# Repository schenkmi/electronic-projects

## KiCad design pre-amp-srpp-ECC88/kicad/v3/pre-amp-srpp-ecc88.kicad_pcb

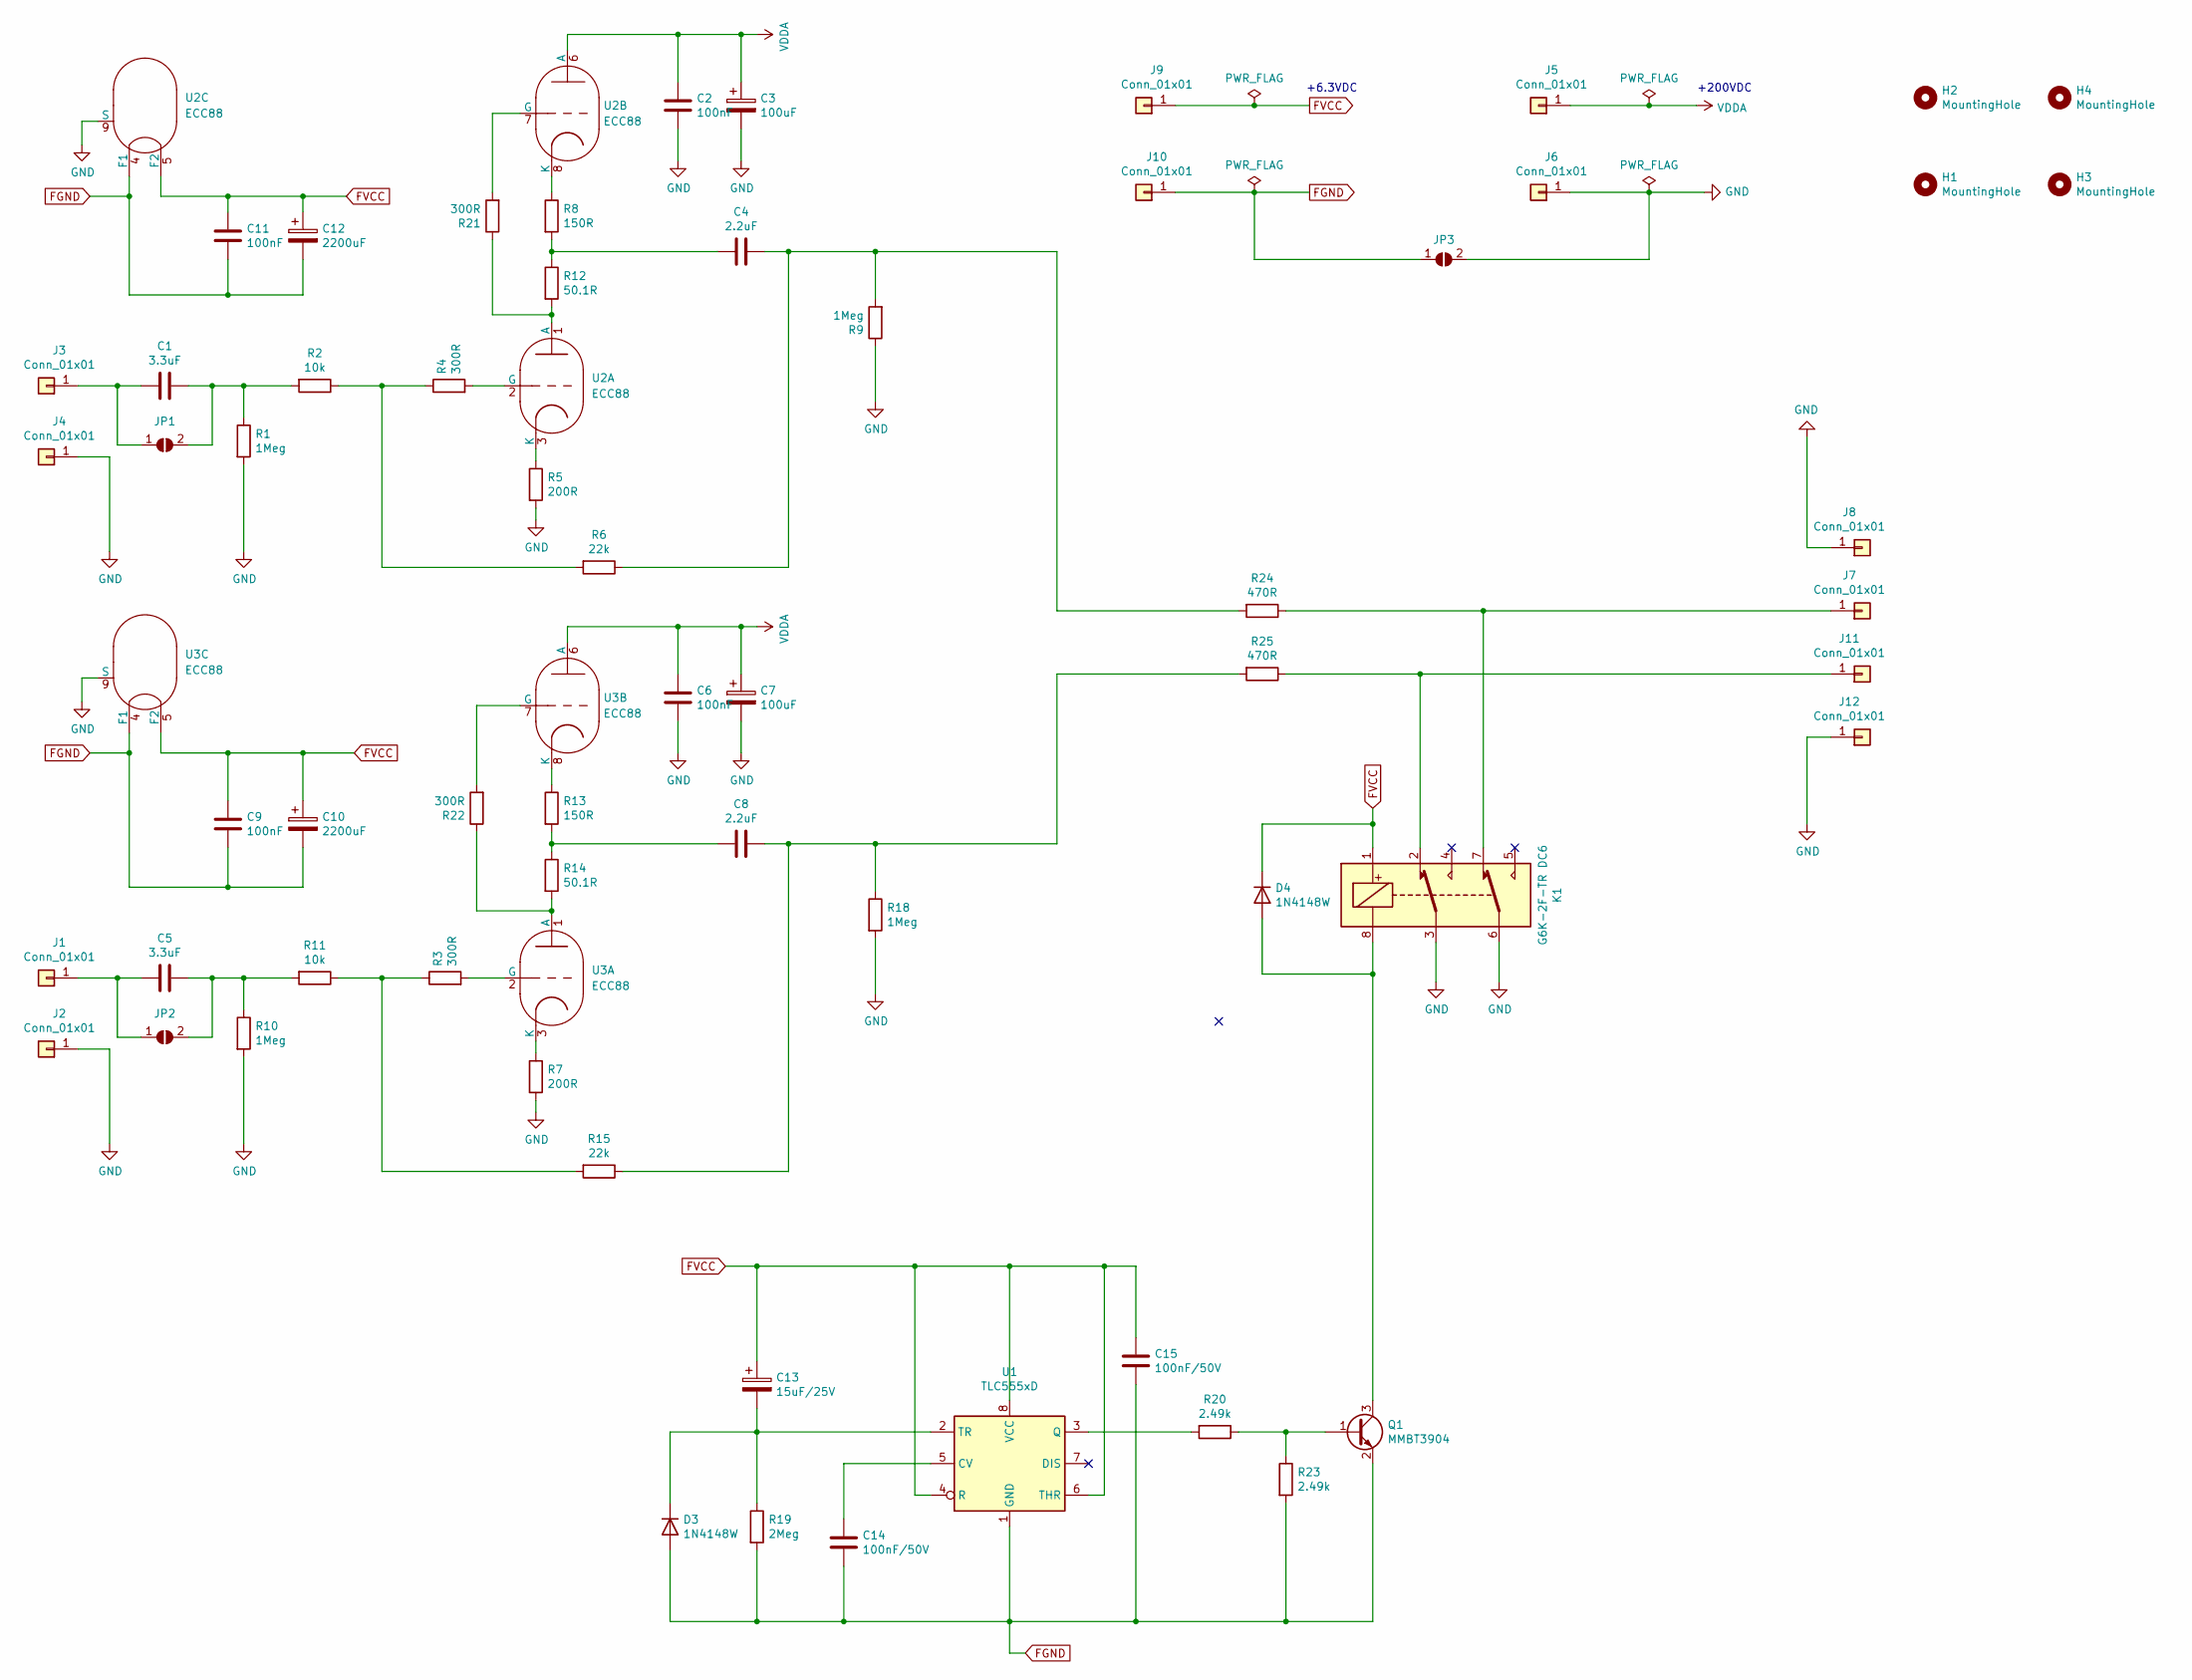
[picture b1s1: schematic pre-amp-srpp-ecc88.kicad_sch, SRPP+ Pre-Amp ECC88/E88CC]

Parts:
C1, C5: 3.3uF; C_Rect_L7.2mm_W7.2mm_P5.00mm_FKS2_FKP2_MKS2_MKP2
C2, C6: 100nF; C_Rect_L16.5mm_W5.0mm_P15.00mm_MKT
C3, C7: 100uF; CP_Radial_D18.0mm_P7.50mm
C4, C8: 2.2uF; C_Rect_L31.5mm_W11.0mm_P27.50mm_MKS4
C9, C11: 100nF; C_Rect_L7.2mm_W2.5mm_P5.00mm_FKS2_FKP2_MKS2_MKP2
C10, C12: 2200uF; CP_Radial_D16.0mm_P7.50mm
C13: 15uF/25V; CP_EIA-3216-12_Kemet-S_Pad1.58x1.35mm_HandSolder
C14, C15: 100nF/50V; C_0805_2012Metric_Pad1.18x1.45mm_HandSolder
D3, D4: 1N4148W; D_SOD-123
H1, H2, H3, H4: MountingHole; MountingHole_3.2mm_M3
J1, J2, J3, J4, J7, J8, J11, J12: Conn_01x01; Pin_D1.0mm_L10.0mm
J5, J6, J9, J10: Conn_01x01; Pin_D1.3mm_L11.0mm
JP1, JP2, JP3: SolderJumper_2_Open; SolderJumper-2_P1.3mm_Open_Pad1.0x1.5mm
K1: G6K-2F-TR DC6; Relay_DPDT_Omron_G6K-2F
Q1: MMBT3904; SOT-23
R1, R9, R10, R18: 1Meg; R_MELF_MMB-0207
R2, R11: 10k; R_MELF_MMB-0207
R3, R4, R21, R22: 300R; R_MELF_MMB-0207
R5, R7: 200R; R_MELF_MMB-0207
R6, R15: 22k; R_MELF_MMB-0207
R8, R13: 150R; R_MELF_MMB-0207
R12, R14: 50.1R; R_MELF_MMB-0207
R19: 2Meg; R_0805_2012Metric_Pad1.20x1.40mm_HandSolder
R20, R23: 2.49k; R_0805_2012Metric_Pad1.20x1.40mm_HandSolder
R24, R25: 470R; R_MELF_MMB-0207
U1: TLC555xD; SOIC-8_3.9x4.9mm_P1.27mm
U2, U3: ECC88; socket_gzc9-b

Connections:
FGND: C9.2, C10.2, C11.2, C12.2, C14.2, C15.2, D3.2 (A), J10.1, JP3.1 (A), Q1.2 (E), R19.2, R23.2, U1.1 (GND), U2.4 (F1), U3.4 (F1)
FVCC: C9.1, C10.1, C11.1, C12.1, C13.1, C15.1, D4.1 (K), J9.1, K1.1, U1.4 (R), U1.6 (THR), U1.8 (VCC), U2.5 (F2), U3.5 (F2)
GND: C2.2, C3.2, C6.2, C7.2, J2.1, J4.1, J6.1, J8.1, J12.1, JP3.2 (B), K1.3, K1.6, R1.2, R5.2, R7.2, R9.1, R10.2, R18.2, U2.9 (S), U3.9 (S)
unnamed: C1.1, JP1.2 (B), R1.1, R2.2
unnamed: C1.2, J3.1, JP1.1 (A)
unnamed: C4.1, R6.1, R9.2, R24.2
unnamed: C4.2, R8.2, R12.1
unnamed: C5.1, JP2.2 (B), R10.1, R11.2
unnamed: C5.2, J1.1, JP2.1 (A)
unnamed: C8.1, R15.1, R18.1, R25.2
unnamed: C8.2, R13.2, R14.1
unnamed: C13.2, D3.1 (K), R19.1, U1.2 (TR)
unnamed: C14.1, U1.5 (CV)
unnamed: D4.2 (A), K1.8, Q1.3 (C)
unnamed: J7.1, K1.7, R24.1
unnamed: J11.1, K1.2, R25.1
unnamed: Q1.1 (B), R20.1, R23.1
unnamed: R2.1, R4.1, R6.2
unnamed: R3.2, U3.2 (G)
unnamed: R4.2, U2.2 (G)
unnamed: R5.1, U2.3 (K)
unnamed: R7.1, U3.3 (K)
unnamed: R8.1, U2.8 (K)
unnamed: R3.1, R11.1, R15.2
unnamed: R12.2, R21.1, U2.1 (A)
unnamed: R13.1, U3.8 (K)
unnamed: R14.2, R22.1, U3.1 (A)
unnamed: R20.2, U1.3 (Q)
unnamed: R21.2, U2.7 (G)
unnamed: R22.2, U3.7 (G)
VDDA: C2.1, C3.1, C6.1, C7.1, J5.1, U2.6 (A), U3.6 (A)

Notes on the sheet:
+6.3VDC
+200VDC

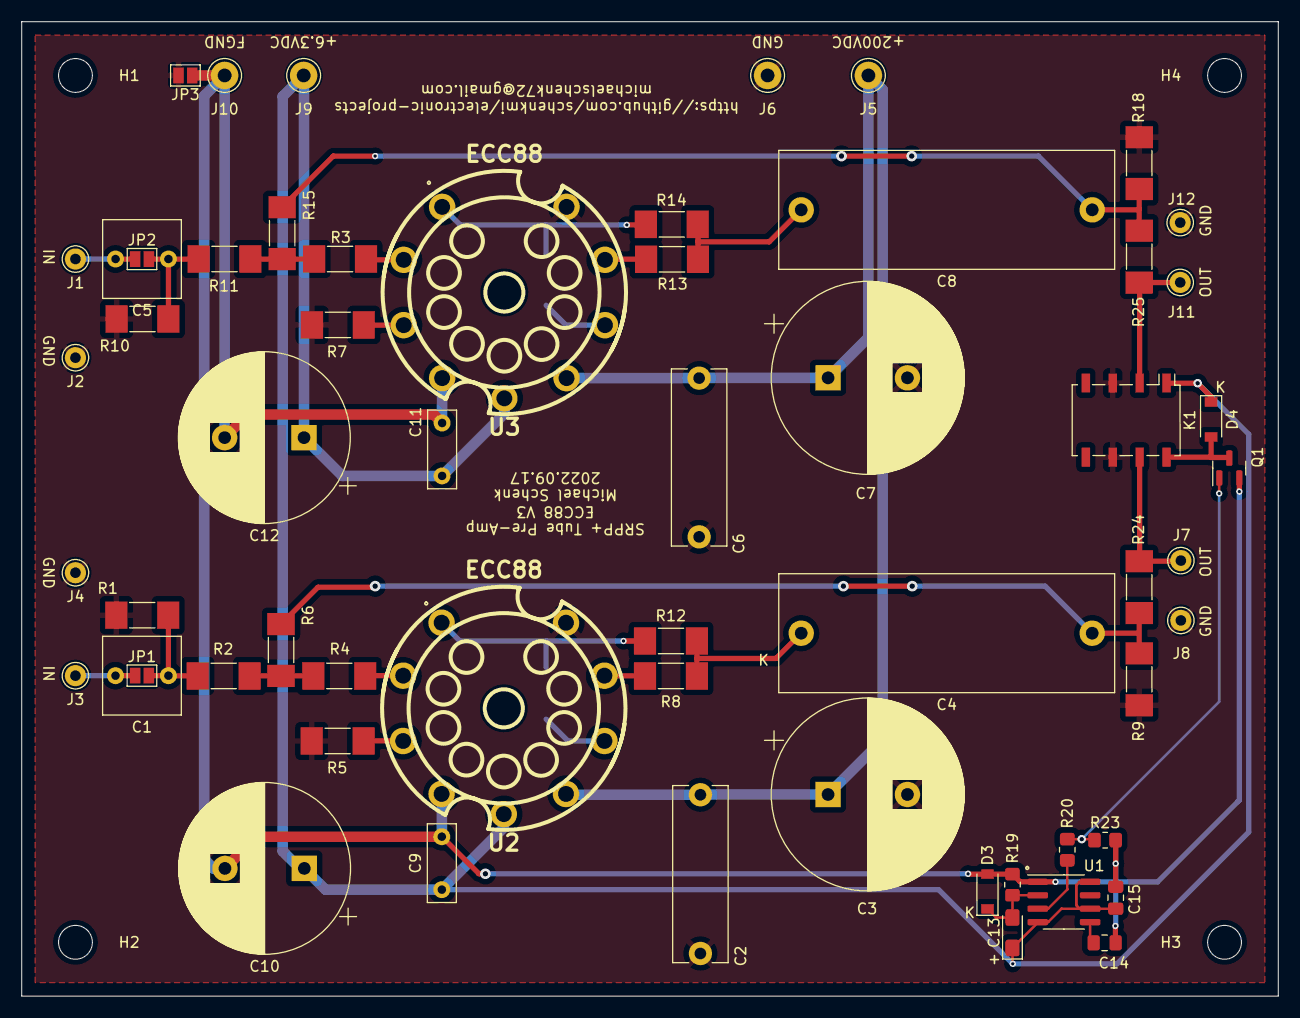
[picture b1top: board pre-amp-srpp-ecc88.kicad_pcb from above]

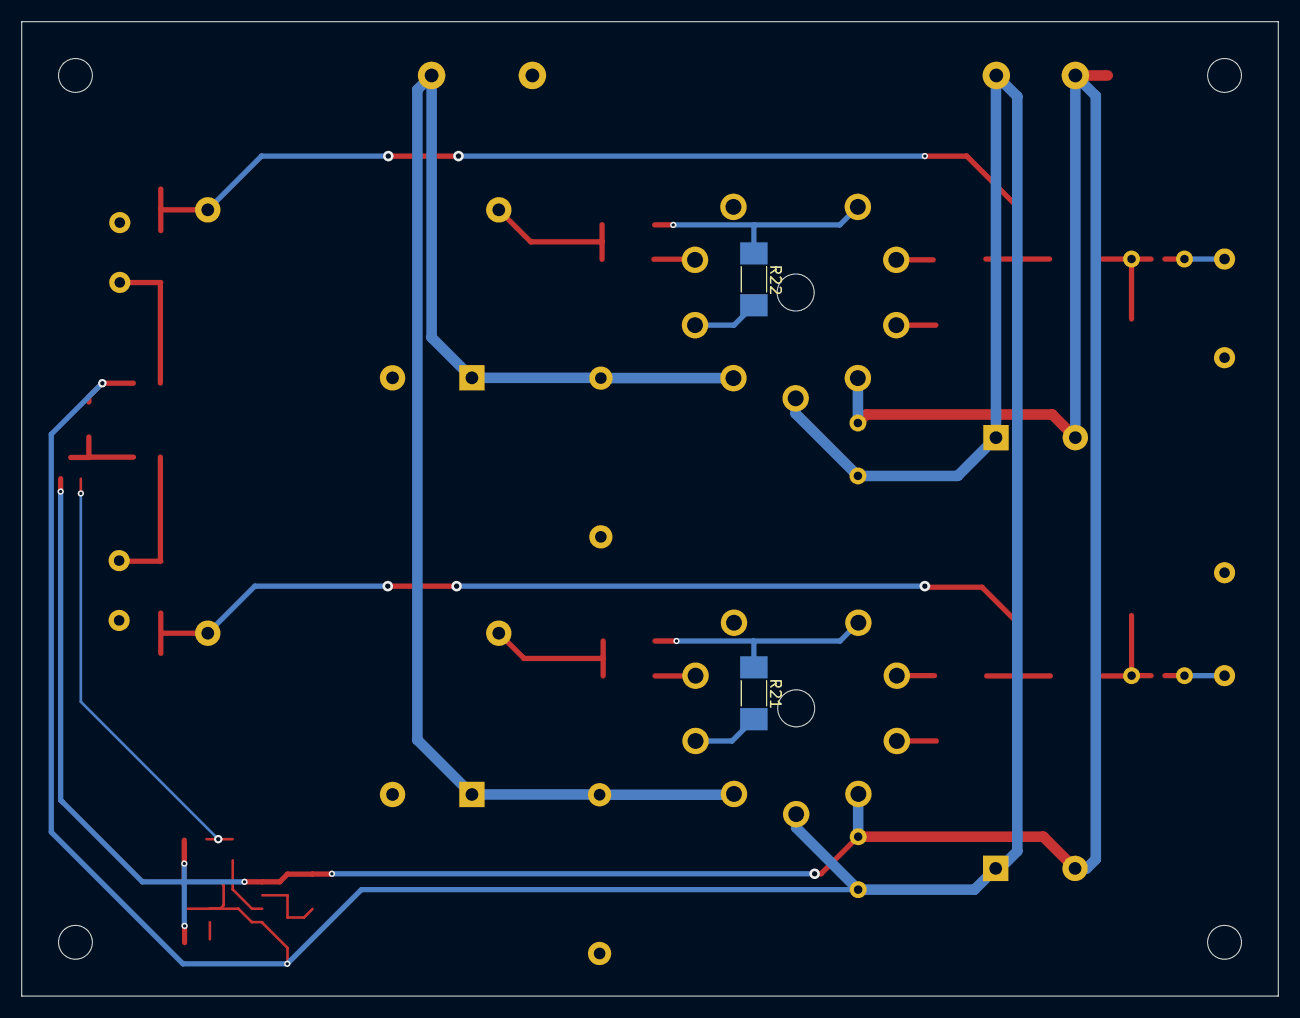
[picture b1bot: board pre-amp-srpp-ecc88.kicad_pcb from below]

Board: 2 copper layers, 118.7 x 92.1 mm, 64 parts (2 on the bottom side), 31 nets.

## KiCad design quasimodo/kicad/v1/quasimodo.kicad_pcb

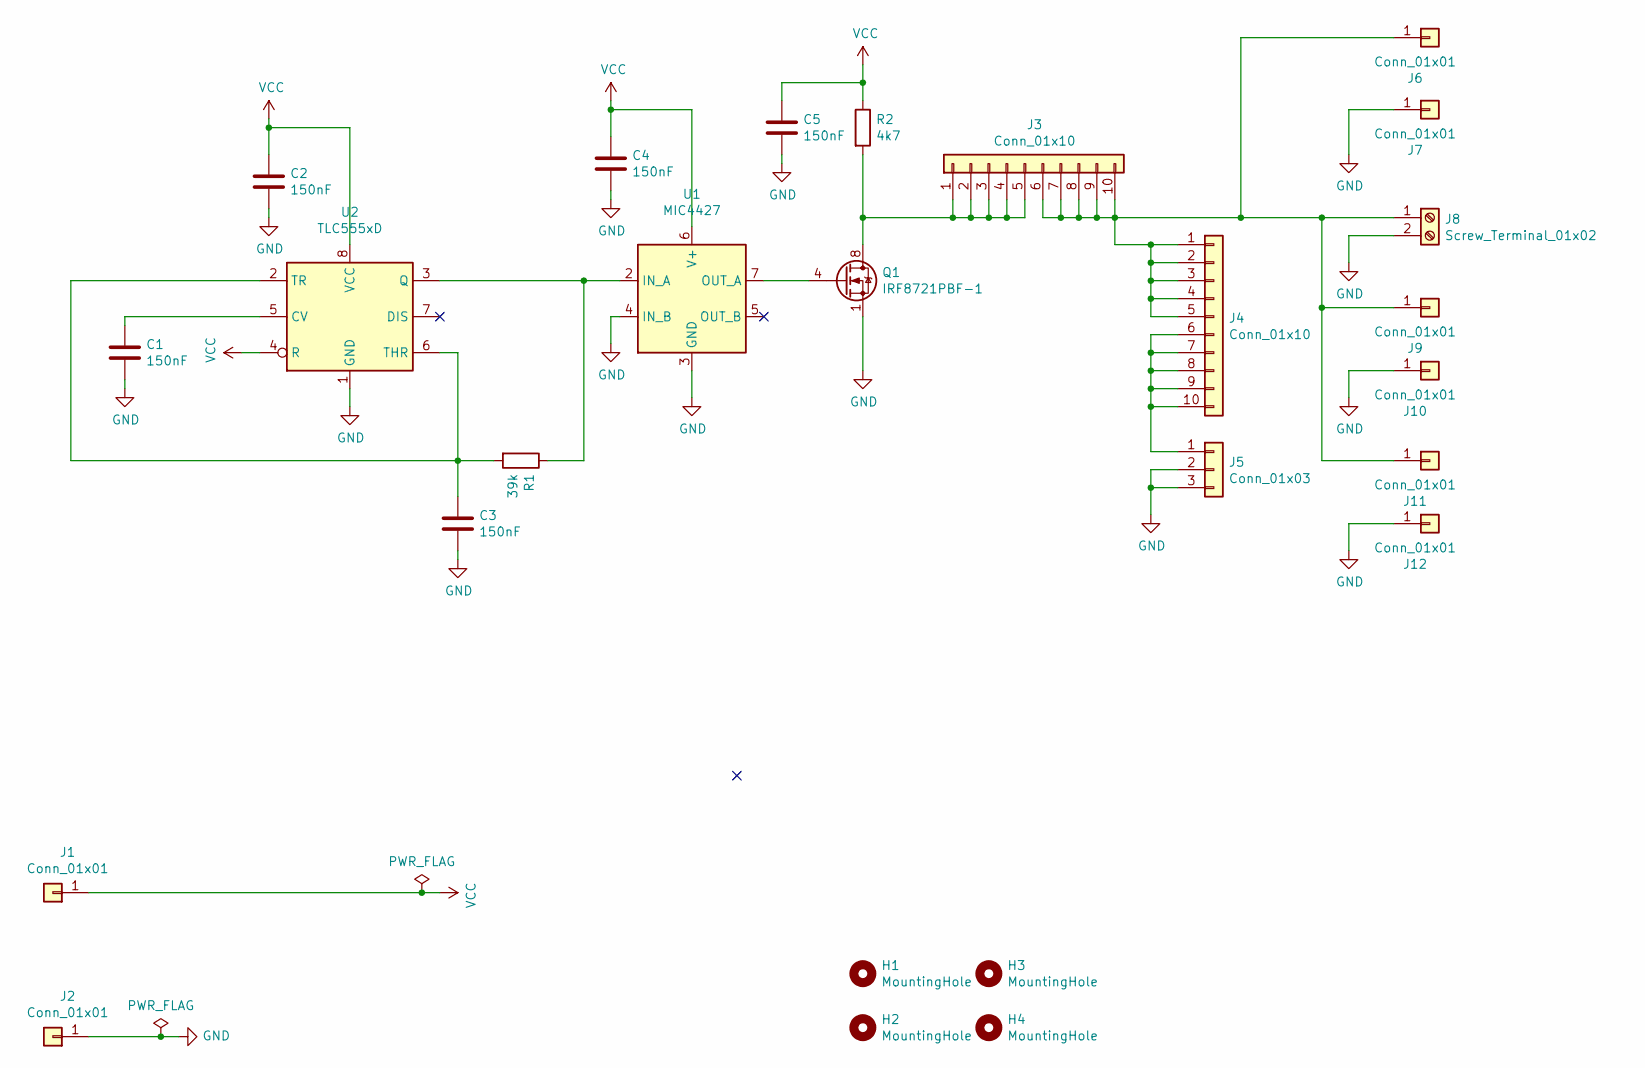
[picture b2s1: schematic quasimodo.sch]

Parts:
C1, C2, C3, C4, C5: 150nF; C_0805_2012Metric_Pad1.18x1.45mm_HandSolder
H1, H2, H3, H4: MountingHole; MountingHole_3.2mm_M3
J1, J2, J6, J7, J9, J10: Conn_01x01; Pin_D1.0mm_L10.0mm
J3, J4: Conn_01x10; PinHeader_1x10_P2.54mm_Vertical
J5: Conn_01x03; PinHeader_1x03_P2.54mm_Vertical
J8: Screw_Terminal_01x02; Molex_KK-254_AE-6410-02A_1x02_P2.54mm_Vertical
J11, J12: Conn_01x01; Pin_D1.3mm_L11.0mm
Q1: IRF8721PBF-1; SOIC-8_3.9x4.9mm_P1.27mm
R1: 39k; R_0805_2012Metric_Pad1.20x1.40mm_HandSolder
R2: 4k7; R_0805_2012Metric_Pad1.20x1.40mm_HandSolder
U1: MIC4427; SOIC-8_3.9x4.9mm_P1.27mm
U2: TLC555xD; SOIC-8_3.9x4.9mm_P1.27mm

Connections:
GND: C1.2, C2.2, C3.2, C4.2, C5.2, J2.1, J5.2, J5.3, J7.1, J8.2, J10.1, J12.1, Q1.1 (S), Q1.2 (S), Q1.3 (S), U1.3 (GND), U1.4 (IN_B), U2.1 (GND)
unnamed: C1.1, U2.5 (CV)
unnamed: C3.1, R1.2, U2.2 (TR), U2.6 (THR)
unnamed: J3.1, J3.2, J3.3, J3.4, J3.5, Q1.5 (D), Q1.6 (D), Q1.7 (D), Q1.8 (D), R2.2
unnamed: J4.6, J4.7, J4.8, J4.9, J4.10, J5.1
unnamed: J3.6, J3.7, J3.8, J3.9, J3.10, J4.1, J4.2, J4.3, J4.4, J4.5, J6.1, J8.1, J9.1, J11.1
unnamed: Q1.4 (G), U1.7 (OUT_A)
unnamed: R1.1, U1.2 (IN_A), U2.3 (Q)
VCC: C2.1, C4.1, C5.1, J1.1, R2.1, U1.6 (V+), U2.4 (R), U2.8 (VCC)

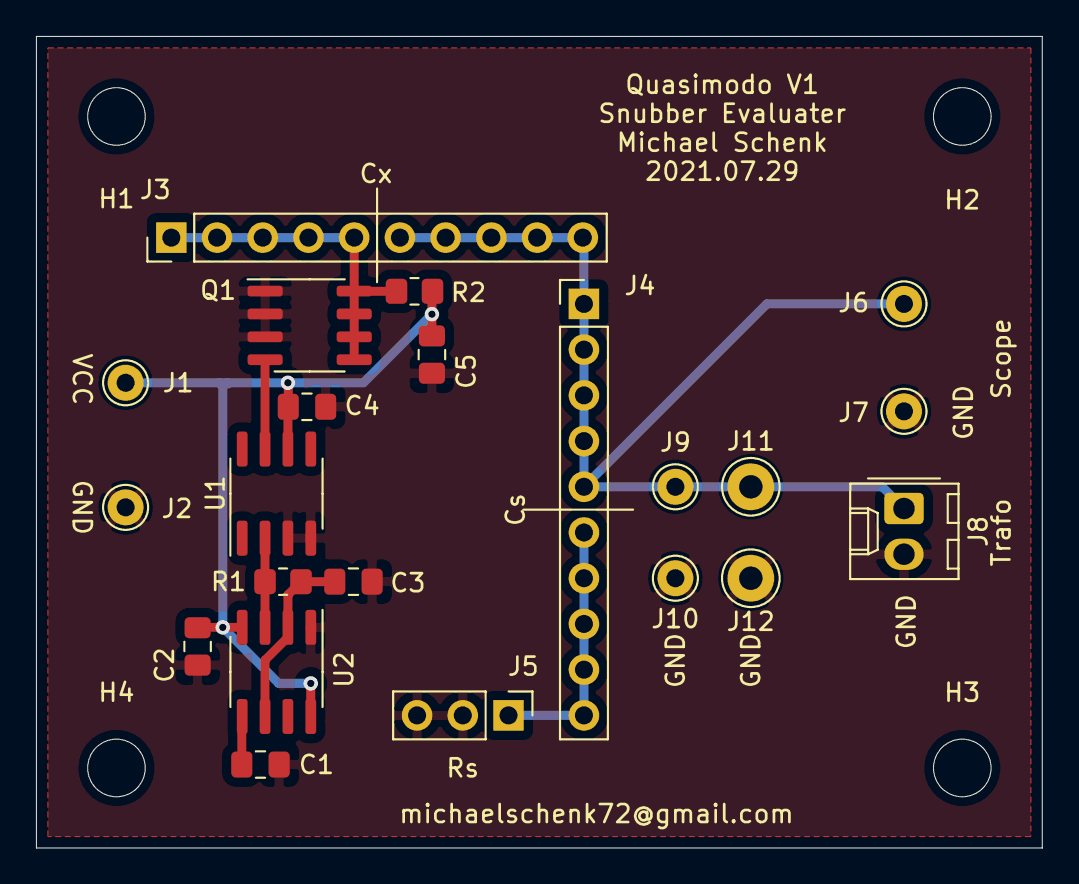
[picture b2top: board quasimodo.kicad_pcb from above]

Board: 2 copper layers, 55.9 x 45.1 mm, 26 parts (0 on the bottom side), 9 nets.
